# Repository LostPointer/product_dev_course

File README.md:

# Курс: Продуктовая разработка бэкенда

**ФАЛТ МФТИ | 2-3 курс**

## О курсе

Двухсеместровый практический курс по разработке современных бэкенд-систем с использованием Python, TypeScript и микросервисной архитектуры.

### Формат
- **Длительность:** 2 семестра (32 недели)
- **Нагрузка:** 1 пара (2 часа) в неделю
- **Формат:** Лекция + практика

### Технологический стек
- **Backend:** Python (aiohttp)
- **Frontend (для интеграции):** TypeScript, React
- **Базы данных:** PostgreSQL, Redis
- **Message Brokers:** RabbitMQ
- **Инфраструктура:** Docker, Docker Compose
- **CI/CD:** GitHub Actions
- **Тестирование:** pytest, testsuite (Yandex)
- **Мониторинг:** Prometheus, Grafana (базово)

## Структура курса

### Семестр 1: Основы бэкенд-разработки (14 учебных недель + 2 резерва)
1. **Модуль 1:** Веб-разработка и API (недели 1-4)
2. **Модуль 2:** Качество и тестирование (недели 5-7)
3. **Модуль 3:** Кэширование и производительность (недели 8-11)
4. **Модуль 4:** API контракты и интеграция с фронтендом (недели 12-14)
5. **Резервные недели:** 15-16 (каникулы, форс-мажоры, догоняющие занятия)

### Семестр 2: Микросервисы и продуктовая разработка (14 учебных недель + 2 резерва)
5. **Модуль 5:** Docker и деплой (недели 1-3)
6. **Модуль 6:** Микросервисная архитектура (недели 4-8)
7. **Модуль 7:** Продвинутые темы (недели 9-11)
8. **Модуль 8:** Финальный проект (недели 12-14)
9. **Резервные недели:** 15-16 (каникулы, форс-мажоры, защиты проектов)

## Навигация по репозиторию

```
product_dev_course/
├── course-materials/           # Материалы курса
│   ├── semester-1/
│   └── semester-2/
├── projects/
│   ├── backend/
│   │   ├── common/             # Общие компоненты и DTO
│   │   ├── libs/               # Внутренние библиотеки/SDK
│   │   └── services/           # Микросервисы платформы
│   │       ├── experiment-service/
│   │       └── auth-service/
│   ├── frontend/
│   │   ├── common/             # Общие UI-компоненты и токены
│   │   ├── libs/               # Фронтенд библиотеки
│   │   └── apps/               # SPA/виджеты
│   │       └── experiment-portal/
│   ├── telemetry_cli/          # CLI для отправки телеметрии в Experiment Service
│   └── rc_vehicle/             # Документация и материалы по RC-модели
├── docs/                       # Документация
├── examples/                   # Примеры кода с занятий
└── README.md
```

## Быстрый старт

### Предварительные требования
- Python 3.14+
- Node.js 24 LTS+
- Docker Desktop
- Git
- Любой редактор кода (VS Code рекомендуется)

### Установка окружения
```bash
# Клонирование репозитория
git clone <repository-url>
cd product_dev_course

# Настройка Python окружения
cd course-materials/semester-1/module-1-web-api/week-01
python -m venv venv
source venv/bin/activate  # Linux/Mac
# или
venv\Scripts\activate  # Windows

# Установка зависимостей
pip install -r requirements.txt
```

Подробная инструкция: [Setup Guide](docs/setup-guide.md)

## Локальный запуск через Docker

Для быстрого запуска всей системы локально используется Docker Compose.

### Быстрый старт с Docker

```bash
# 1. Подготовка окружения
cp env.docker.example .env
cp docker-compose.override.yml.example docker-compose.override.yml

# 2. Запуск в development режиме (с hot-reload)
docker-compose up

# 3. Или в фоновом режиме
docker-compose up -d

# 4. Просмотр логов
docker-compose logs -f

# 5. Остановка
docker-compose down
```

### Доступные сервисы

После запуска доступны:
- **Experiment Portal (Frontend):** http://localhost:3000 (dev режим с hot-reload)
- **Experiment Service API:** http://localhost:8002
- **Auth Service:** http://localhost:8001
- **Auth Proxy (BFF):** http://localhost:8080
- **Grafana (Logging):** http://localhost:3001 (логин: admin, пароль: admin)
- **PostgreSQL:** localhost:5433 (порт 5433 чтобы не конфликтовать с локальным PostgreSQL на 5432)
  - База данных `experiment_db` для experiment-service
  - База данных `auth_db` для auth-service

### Режимы работы

- **Development режим** (по умолчанию): hot-reload, volumes для исходного кода, dev команды
- **Production режим:** оптимизированные образы, без hot-reload
  ```bash
  docker-compose -f docker-compose.yml up
  ```

### Документация

Подробная документация по локальной разработке:
- [Инвентаризация сервисов](docs/local-dev-inventory.md)
- [Нормализация окружения](docs/local-dev-env-normalization.md)
- [Настройка Docker и hot-reload](docs/local-dev-docker-setup.md)
- [Ручное тестирование (E2E)](docs/manual-testing.md)

## Итоговый проект

Микросервисная система сбора и отображения экспериментов (Experiment Tracking Platform) с 6 сервисами на Python:
- Auth Service - аутентификация и управление пользователями, проектами
- Experiment Service - регистрация и хранение экспериментов
- Metrics Service - сбор и хранение метрик (accuracy, loss, и т.д.)
- Artifact Service - хранение артефактов (модели, графики, логи)
- Comparison Service - сравнение экспериментов
- API Gateway - единая точка входа, агрегация данных

Опционально: Frontend на TypeScript + React для визуализации экспериментов и дашбордов.

Студенты работают через Pull Requests, проводят code review и улучшают архитектуру системы.

**Техническое задание:** полное описание требований, архитектуры и критериев приемки доступно в `docs/experiment-tracking-ts.md`. Рекомендовано ознакомиться перед началом работы над итоговым проектом.

**Статус и roadmap платформы:** см. `docs/experiment-tracking-status-and-roadmap.md`.

## Карта сервисов

### Архитектурная диаграмма

```mermaid
graph TB
    subgraph Frontend["🌐 Frontend Layer"]
        Portal["Experiment Portal<br/>React SPA<br/>✅ Реализован<br/>:3000/:80"]
        AuthProxy["Auth Proxy<br/>nginx<br/>✅ Реализован<br/>:8080"]
    end

    subgraph GatewayLayer["🚪 API Gateway Layer"]
        Gateway["API Gateway<br/>Единая точка входа<br/>🚧 Планируется"]
    end

    subgraph Backend["⚙️ Backend Services"]
        AuthSvc["Auth Service<br/>Аутентификация, JWT<br/>🚧 Планируется"]
        ExpSvc["Experiment Service<br/>Эксперименты, запуски<br/>✅ Реализован<br/>:8002"]
        MetricsSvc["Metrics Service<br/>Метрики, временные ряды<br/>🚧 Планируется"]
        ArtifactSvc["Artifact Service<br/>Файлы, модели<br/>🚧 Планируется"]
        CompareSvc["Comparison Service<br/>Сравнение экспериментов<br/>🚧 Планируется"]
        TelemetrySvc["Telemetry Ingest<br/>Потоки телеметрии<br/>🚧 Планируется"]
    end

    subgraph Infrastructure["🏗️ Infrastructure"]
        Postgres[("PostgreSQL<br/>Основная БД<br/>:5432")]
        Redis[("Redis<br/>Кэш, rate limiting<br/>:6379")]
        RabbitMQ["RabbitMQ<br/>Message Broker<br/>:5672"]
        S3[("S3 Storage<br/>Артефакты<br/>🚧 Планируется")]
    end

    Portal -->|HTTP| AuthProxy
    AuthProxy -->|Proxy| Gateway
    Gateway -->|REST API| AuthSvc
    Gateway -->|REST API| ExpSvc
    Gateway -->|REST API| MetricsSvc
    Gateway -->|REST API| ArtifactSvc
    Gateway -->|REST API| CompareSvc

    TelemetrySvc -->|Publish| RabbitMQ
    RabbitMQ -->|Subscribe| MetricsSvc

    AuthSvc -->|SQL| Postgres
    ExpSvc -->|SQL| Postgres
    MetricsSvc -->|SQL| Postgres
    CompareSvc -->|SQL| Postgres
    TelemetrySvc -->|SQL| Postgres

    ArtifactSvc -->|Metadata| Postgres
    ArtifactSvc -->|Files| S3

    ExpSvc -->|Cache| Redis
    AuthSvc -->|Cache| Redis
    Gateway -->|Rate Limit| Redis

    ExpSvc -.->|Events| RabbitMQ
    MetricsSvc -.->|Events| RabbitMQ
    ArtifactSvc -.->|Events| RabbitMQ

    style ExpSvc fill:#90EE90,stroke:#2E7D32,stroke-width:3px
    style Portal fill:#90EE90,stroke:#2E7D32,stroke-width:3px
    style AuthProxy fill:#90EE90,stroke:#2E7D32,stroke-width:3px
    style AuthSvc fill:#FFE4B5,stroke:#FF8C00,stroke-width:2px
    style MetricsSvc fill:#FFE4B5,stroke:#FF8C00,stroke-width:2px
    style ArtifactSvc fill:#FFE4B5,stroke:#FF8C00,stroke-width:2px
    style CompareSvc fill:#FFE4B5,stroke:#FF8C00,stroke-width:2px
    style Gateway fill:#FFE4B5,stroke:#FF8C00,stroke-width:2px
    style TelemetrySvc fill:#FFE4B5,stroke:#FF8C00,stroke-width:2px
    style S3 fill:#FFE4B5,stroke:#FF8C00,stroke-width:2px
    style Postgres fill:#E3F2FD,stroke:#1976D2
    style Redis fill:#FFEBEE,stroke:#D32F2F
    style RabbitMQ fill:#F3E5F5,stroke:#7B1FA2
```

### Backend сервисы

| Сервис | Статус | Описание | Порт | База данных |
|--------|--------|----------|------|-------------|
| **Experiment Service** | ✅ Реализован | Регистрация и хранение экспериментов, запусков, capture sessions, датчиков | 8002 | PostgreSQL |
| **Auth Service** | 🚧 Планируется | Аутентификация и управление пользователями, проектами, JWT токены | - | PostgreSQL |
| **Metrics Service** | 🚧 Планируется | Сбор и хранение метрик (accuracy, loss и т.д.), исторические серии | - | PostgreSQL/Timescale |
| **Artifact Service** | 🚧 Планируется | Хранение артефактов (модели, графики, логи), версионирование | - | S3 + PostgreSQL |
| **Comparison Service** | 🚧 Планируется | Сравнение экспериментов, расчёт дельт по метрикам | - | PostgreSQL |
| **API Gateway** | 🚧 Планируется | Единая точка входа, агрегация данных от сервисов, маршрутизация | - | - |
| **Telemetry Ingest** | 🚧 Планируется | Приём потоков телеметрии, конвертация raw→physical значений | - | Kafka/Redis + PostgreSQL |

### Frontend приложения

| Приложение | Статус | Описание | Порт |
|------------|--------|----------|------|
| **Experiment Portal** | ✅ Реализован | React SPA для визуализации экспериментов и дашбордов | 3000 (dev), 80 (prod) |
| **Auth Proxy** | ✅ Реализован | Прокси для аутентификации и маршрутизации запросов | 8080 |

### Инфраструктурные сервисы

| Сервис | Описание | Порт |
|--------|----------|------|
| **PostgreSQL** | Основная база данных для всех сервисов | 5432 |
| **Redis** | Кэширование, rate limiting, сессии | 6379 |
| **RabbitMQ** | Message broker для event-driven коммуникации | 5672 (AMQP), 15672 (Management UI) |

### Легенда статусов
- ✅ **Реализован** - сервис полностью реализован и готов к использованию
- 🚧 **Планируется** - сервис в планах разработки

## Система оценивания

### Семестр 1 (50%)
- Практические задания: 30%
- Промежуточное тестирование: 10%
- Итоговое задание: 10%

### Семестр 2 (50%)
- Практические задания: 20%
- Pull Requests в проект: 20%
- Code Review: 5%
- Финальная защита: 5%

### Бонусы
- Рефакторинг кода: +5 баллов
- Добавление тестов: +5 баллов
- Улучшение документации: +5 баллов

### Шкала оценок (1-10)
- 10: Outstanding (95-115 баллов)
- 9: Excellent (90-94)
- 8: Very Good (85-89)
- 7: Good (75-84)
- 6: Satisfactory (65-74)
- 5: Adequate (55-64) - минимальный проходной
- 4 и ниже: не сдал

Подробнее: [Grading System](docs/grading-system.md)

## Полезные ресурсы

### Документация
- [aiohttp](https://docs.aiohttp.org/)
- [SQLAlchemy](https://docs.sqlalchemy.org/)
- [Docker](https://docs.docker.com/)
- [PostgreSQL](https://www.postgresql.org/docs/)
- [OpenAPI/Swagger](https://swagger.io/specification/)

### Книги
- "Designing Data-Intensive Applications" - Martin Kleppmann
- "Building Microservices" - Sam Newman
- "Clean Architecture" - Robert Martin

### Онлайн-курсы
- [aiohttp Tutorial](https://docs.aiohttp.org/en/stable/web_quickstart.html)
- [Docker for Beginners](https://docker-curriculum.com/)

## Связь

- **Вопросы по заданиям:** GitHub Issues в репозитории курса
- **Code Review:** Pull Requests в backend-project
- **Общие вопросы:** Telegram-чат курса

## Лицензия

Материалы курса доступны для образовательных целей.

---

**Добро пожаловать на курс! Удачи в изучении бэкенд-разработки! 🚀**

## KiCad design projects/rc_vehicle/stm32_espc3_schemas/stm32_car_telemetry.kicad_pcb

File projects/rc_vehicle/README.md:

# rc_vehicle

Проект про **управление RC‑моделью** (ретрофит): STM32 делает real‑time управление ESC/серво и сбор IMU, ESP32 поднимает Wi‑Fi (web‑пульт) и общается со STM32 по UART.

Сейчас здесь **документационный скелет**: требования, протоколы, договорённости. Реализация прошивок будет добавлена позже.

## Выбранная база (шасси)
- **Himoto SCT‑16 4WD RTR 1:16 2.4G (HI4192|RED)** — [карточка на Яндекс Маркете](https://market.yandex.ru/card/radioupravlyayemyy-short-kors-trak-himoto-sct-16-4wd-rtr-masshtab-116-24g---hi4192red/4399880474?do-waremd5=9jRAzA7SdRMQfoiYw52cAw&cpc=d2PGwzy0QTs0eLnRlKp0k5YCu2JHodVzFJDvJtshUWzSyDz3E9FKzWqRWc9gIULXX9EJ9Ku-0mvQsCTCCBzwqE-a6FjyS4PfsjEQ8zw1WU-FqmGO5HghkO4aplP4qdbhCmxXetVCLQqycN6o03nHXP_tLSTfOP2glbQ73t_oCvPUAJbjP6PtzyvAx9EZdLsM_MZD6JCx9hF2cmhA0Yc88aMXOZ_Ei1IVvZjbvcsvgHDewTubfOP7WxmSPsCnzZvbiXsTE30oPZ2PX6ct5WAkjK3DLf9791pMdJqhKAAkwv7LcDElOfELc6S0wxkUen63wrtSxWiKAo38hVIlcprRM84HQu9ao5TKsC9LjxYBM0hP5J5NaEfI0IHukClWKjyg9bwUETyJZKEokhHrUvGdfPVfDCgSMMCBr0cFhxl4T4GRgdt4k6KP_xjqOGhNoV-7&ogV=-9)

## Telemetry agent
CLI/агент для отправки телеметрии в Experiment Service вынесен в отдельный проект:
- `projects/telemetry_cli`

## Область ответственности
- управление (RC‑пульт и Wi‑Fi), приоритет RC > Wi‑Fi
- failsafe при потере источника управления
- IMU чтение и выдача телеметрии в web‑пульт (и/или наружу в будущем)

## Документация
- `docs/ts.md` — краткое ТЗ и критерии приёмки (MVP).
- `docs/interfaces_protocols.md` — протоколы: WebSocket (ESP32↔браузер) и UART кадры (ESP32↔RP2040).
- `docs/wiring_diagram.md` — **схема подключения компонентов** (ESP32, RP2040, IMU, ESC, Servo, RC приёмник).
- `docs/wiring_diagram.drawio` — визуальная схема для редактирования в draw.io.
- `docs/ai_schematic_tools.md` — инструменты и AI для генерации схем.
- `docs/glossary_ru.md` — глоссарий терминов и сокращений (ESC, BEC, PWM, IMU и т.д.).
- `docs/cpp_coding_style.md` — стиль кода для прошивок (C++): Google Style Guide, расширения `.hpp`, правила форматирования.
- `docs/firmware_timing.md` — тайминги и частоты для прошивок.
- `docs/stabilization/` — документация системы стабилизации (роудмап разработки).
- (вне проекта) `docs/telemetry-rc-stm32.md` — рекомендации по формату телеметрии для Experiment Service, если будем экспортировать данные в ingest.

## Структура проекта
- `firmware/rp2040/` — прошивка RP2040 (PWM, RC‑in, IMU, failsafe, UART протокол) — *в разработке*
- `firmware/esp32/` — прошивка ESP32‑S3 (AP + web UI + WS + UART мост) — *в разработке*
- `docs/` — спецификации и схемы
  - `firmware_timing.md` — тайминги и частоты для прошивок

## Сборка прошивок

Для удобной сборки обеих прошивок используется Makefile в корне проекта:

```bash
# Показать все доступные команды
make help

# Собрать обе прошивки
make all

# Собрать только ESP32
make esp32-build

# Собрать только RP2040
make rp2040-build

# Очистить все проекты
make clean
```

Подробные инструкции по сборке каждой прошивки:
- ESP32: см. `firmware/esp32/README.md`
- RP2040: см. `firmware/rp2040/README.md`

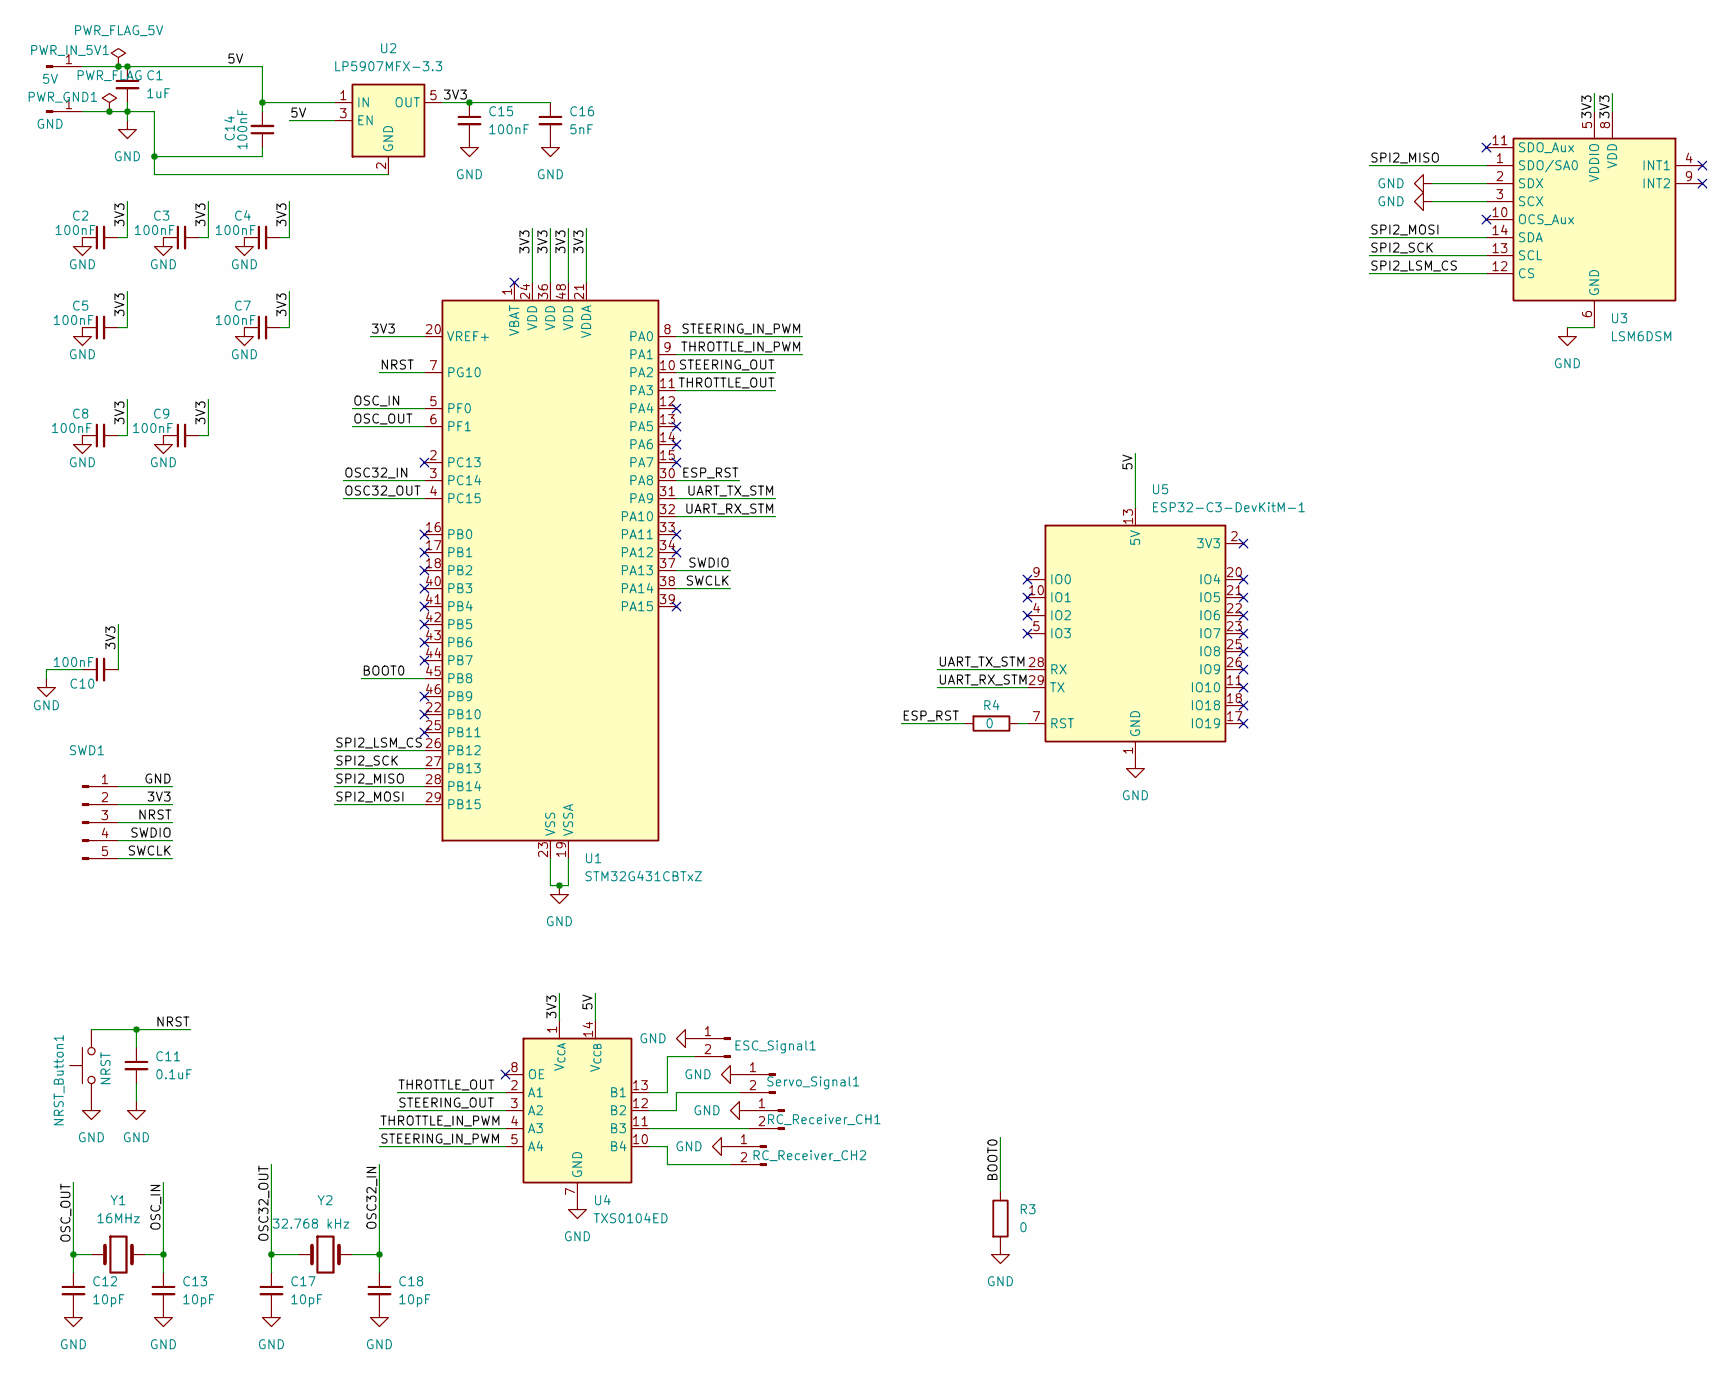
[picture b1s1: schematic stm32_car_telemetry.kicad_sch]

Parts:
C1: 1uF; C_0805_2012Metric
C2, C3, C4, C5, C7, C8, C9, C10: 100nF; C_0201_0603Metric
C11: 0.1uF; C_0805_2012Metric
C12, C13, C17, C18: 10pF; C_01005_0402Metric
C14, C15: 100nF; C_0805_2012Metric
C16: 5nF; C_0805_2012Metric
ESC_Signal1: Conn_01x02_Pin; PinHeader_1x02_P2.54mm_Vertical
NRST_Button1: NRST; SW_SPST_PTS810
PWR_GND1: GND; PinSocket_1x01_P2.54mm_Vertical
PWR_IN_5V1: 5V; PinSocket_1x01_P2.54mm_Vertical
R3, R4: 0; R_0201_0603Metric
RC_Receiver_CH1, RC_Receiver_CH2: Conn_01x02_Pin; PinHeader_1x02_P2.54mm_Vertical
SWD1: Conn_01x05_Pin; PinHeader_1x05_P2.54mm_Vertical
Servo_Signal1: Conn_01x02_Pin; PinHeader_1x02_P2.54mm_Vertical
U1: STM32G431CBTxZ; LQFP-48_7x7mm_P0.5mm
U2: LP5907MFX-3.3; SOT-23-5
U3: LSM6DSM; LGA-14_3x2.5mm_P0.5mm_LayoutBorder3x4y
U4: TXS0104ED; SOIC-14_3.9x8.7mm_P1.27mm
U5: ESP32-C3-DevKitM-1
Y1: 16MHz; Crystal_SMD_3225-4Pin_3.2x2.5mm
Y2: 32.768 kHz; Crystal_SMD_3225-4Pin_3.2x2.5mm

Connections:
/3V3: C2.2, C3.2, C4.2, C5.2, C7.2, C8.2, C9.2, C10.2, C15.1, C16.1, SWD1.2, U1.20 (VREF+), U1.21 (VDDA), U1.24 (VDD), U1.36 (VDD), U1.48 (VDD), U2.5 (OUT), U3.5 (VDDIO), U3.8 (VDD), U4.1 (V_{CCA})
/5V: C1.1, C14.2, PWR_IN_5V1.1, U2.1 (IN), U2.3 (EN), U4.14 (V_{CCB}), U5.13 (5V), U5.14 (5V)
/BOOT0: R3.1, U1.45 (PB8)
/ESP_RST: R4.2, U1.30 (PA8)
/NRST: C11.1, NRST_Button1.2, SWD1.3, U1.7 (PG10)
/OSC32_IN: C18.1, U1.3 (PC14), Y2.2
/OSC32_OUT: C17.1, U1.4 (PC15), Y2.1
/OSC_IN: C13.1, U1.5 (PF0), Y1.2
/OSC_OUT: C12.1, U1.6 (PF1), Y1.1
/SPI2_LSM_CS: U1.26 (PB12), U3.12 (CS)
/SPI2_MISO: U1.28 (PB14), U3.1 (SDO/SA0)
/SPI2_MOSI: U1.29 (PB15), U3.14 (SDA)
/SPI2_SCK: U1.27 (PB13), U3.13 (SCL)
/STEERING_IN_PWM: U1.8 (PA0), U4.5 (A4)
/STEERING_OUT: U1.10 (PA2), U4.3 (A2)
/SWCLK: SWD1.5, U1.38 (PA14)
/SWDIO: SWD1.4, U1.37 (PA13)
/THROTTLE_IN_PWM: U1.9 (PA1), U4.4 (A3)
/THROTTLE_OUT: U1.11 (PA3), U4.2 (A1)
/UART_RX_STM: U1.32 (PA10), U5.29 (TX)
/UART_TX_STM: U1.31 (PA9), U5.28 (RX)
GND: C1.2, C2.1, C3.1, C4.1, C5.1, C7.1, C8.1, C9.1, C10.1, C11.2, C12.2, C13.2, C14.1, C15.2, C16.2, C17.2, C18.2, ESC_Signal1.1, NRST_Button1.1, PWR_GND1.1, R3.2, RC_Receiver_CH1.1, RC_Receiver_CH2.1, SWD1.1, Servo_Signal1.1, U1.19 (VSSA), U1.23 (VSS), U1.35 (VSS), U1.47 (VSS), U2.2 (GND), U3.2 (SDX), U3.3 (SCX), U3.6 (GND), U3.7 (GND), U4.7 (GND), U5.1 (GND), U5.6 (GND), U5.8 (GND), U5.12 (GND), U5.15 (GND), U5.16 (GND), U5.19 (GND), U5.24 (GND), U5.27 (GND), U5.30 (GND)
unnamed: ESC_Signal1.2, U4.13 (B1)
unnamed: RC_Receiver_CH1.2, U4.11 (B3)
unnamed: RC_Receiver_CH2.2, U4.10 (B4)
unnamed: Servo_Signal1.2, U4.12 (B2)
unnamed: R4.1, U5.7 (RST)

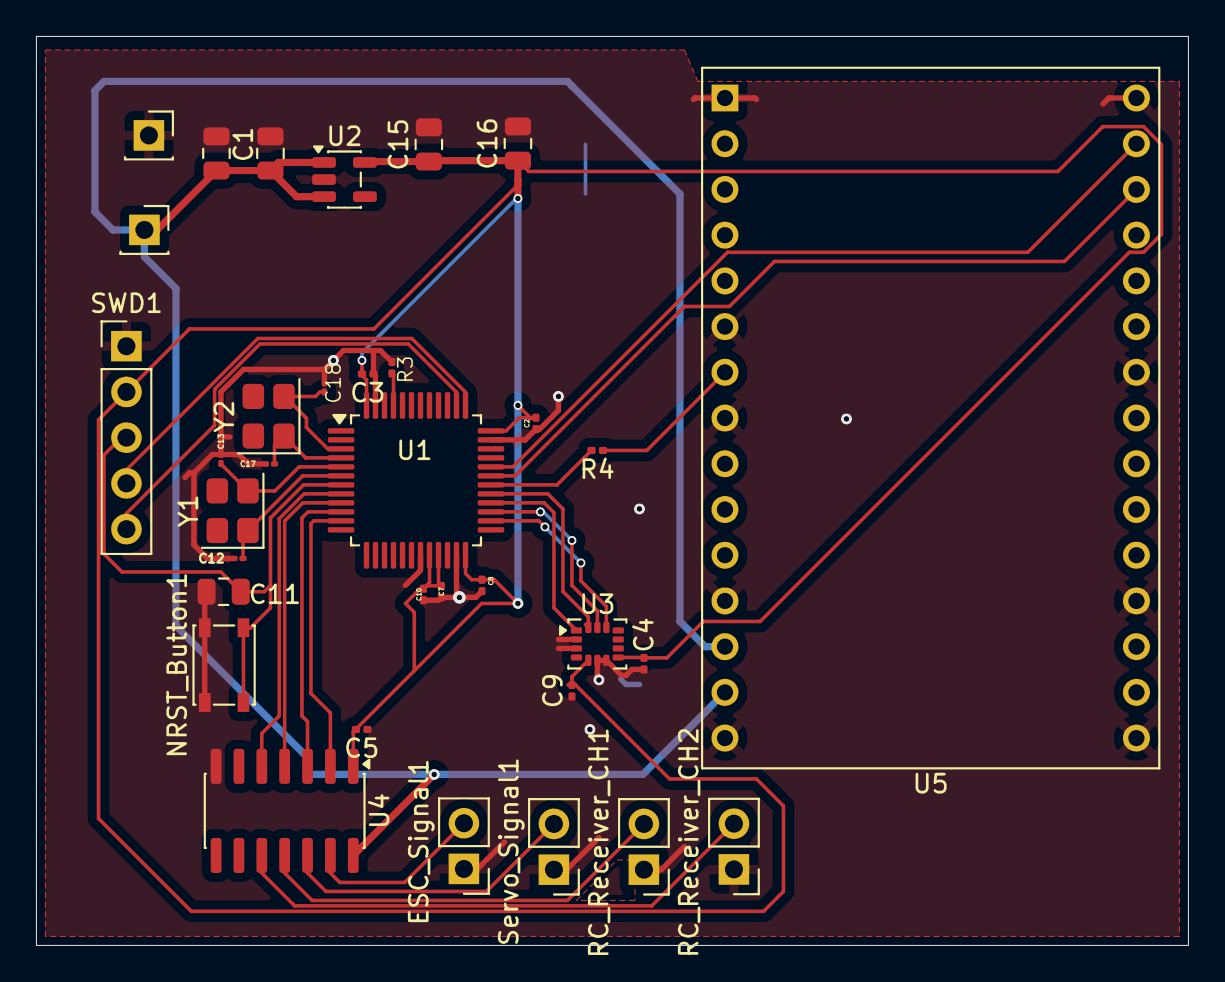
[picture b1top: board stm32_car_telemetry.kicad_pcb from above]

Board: 2 copper layers, 64.0 x 50.5 mm, 34 parts (0 on the bottom side), 27 nets.

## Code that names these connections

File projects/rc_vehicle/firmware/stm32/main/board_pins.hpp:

#pragma once

// Пины и периферия по семейству MCU (STM32Cube LL).
// Используются в uart_bridge, pwm_control, rc_input, imu (SPI).
// Порты: GPIOA, GPIOB (STM32Cube). Пины: номер 0..15 или маска LL_GPIO_PIN_x.

#if !defined(STM32F1) && !defined(STM32F4) && !defined(STM32G4)
#define STM32F1 1  // Fallback для IDE
#endif

#if defined(STM32F1)
// Blue Pill STM32F103C8: USART2 (PA2/PA3), TIM2 CH1/CH2 (PA0/PA1), RC-in PA4/PA5, IMU SPI2 PB12/PB13/PB14/PB15
#define UART_USART       USART2
#define UART_GPIO_PORT   GPIOA
#define UART_TX_PIN      2
#define UART_RX_PIN      3
#define PWM_TIM          TIM2
#define PWM_THROTTLE_PORT GPIOA
#define PWM_THROTTLE_PIN  0
#define PWM_STEERING_PORT GPIOA
#define PWM_STEERING_PIN  1
#define RC_IN_THROTTLE_PORT  GPIOA
#define RC_IN_THROTTLE_PIN   4
#define RC_IN_STEERING_PORT  GPIOA
#define RC_IN_STEERING_PIN   5
// IMU MPU-6050 по SPI2 (PB13 SCK, PB14 MISO, PB15 MOSI, PB12 NCS)
#define SPI_PERIPH       SPI2
#define SPI_SCK_PORT     GPIOB
#define SPI_SCK_PIN      13
#define SPI_MISO_PORT    GPIOB
#define SPI_MISO_PIN     14
#define SPI_MOSI_PORT    GPIOB
#define SPI_MOSI_PIN     15
#define SPI_NCS_PORT     GPIOB
#define SPI_NCS_PIN      12

#elif defined(STM32F4)
// Black Pill STM32F411: USART2 (PA2/PA3), TIM2 CH1/CH2 (PA0/PA1), RC-in PA4/PA5, IMU SPI2 PB12–PB15
#define UART_USART       USART2
#define UART_GPIO_PORT   GPIOA
#define UART_TX_PIN      2
#define UART_RX_PIN      3
#define PWM_TIM          TIM2
#define PWM_THROTTLE_PORT GPIOA
#define PWM_THROTTLE_PIN  0
#define PWM_STEERING_PORT GPIOA
#define PWM_STEERING_PIN  1
#define RC_IN_THROTTLE_PORT  GPIOA
#define RC_IN_THROTTLE_PIN   4
#define RC_IN_STEERING_PORT  GPIOA
#define RC_IN_STEERING_PIN   5
// IMU MPU-6050 по SPI2
#define SPI_PERIPH       SPI2
#define SPI_SCK_PORT     GPIOB
#define SPI_SCK_PIN      13
#define SPI_MISO_PORT    GPIOB
#define SPI_MISO_PIN     14
#define SPI_MOSI_PORT    GPIOB
#define SPI_MOSI_PIN     15
#define SPI_NCS_PORT     GPIOB
#define SPI_NCS_PIN      12

#elif defined(STM32G4)
// STM32G431CB: USART2 (PA2/PA3), TIM2, RC-in, IMU SPI2 — настройте под схему
#define UART_USART       USART2
#define UART_GPIO_PORT   GPIOA
#define UART_TX_PIN      2
#define UART_RX_PIN      3
#define PWM_TIM          TIM2
#define PWM_THROTTLE_PORT GPIOA
#define PWM_THROTTLE_PIN  0
#define PWM_STEERING_PORT GPIOA
#define PWM_STEERING_PIN  1
#define RC_IN_THROTTLE_PORT  GPIOA
#define RC_IN_THROTTLE_PIN   4
#define RC_IN_STEERING_PORT  GPIOA
#define RC_IN_STEERING_PIN   5
// IMU MPU-6050 по SPI2
#define SPI_PERIPH       SPI2
#define SPI_SCK_PORT     GPIOB
#define SPI_SCK_PIN      13
#define SPI_MISO_PORT    GPIOB
#define SPI_MISO_PIN     14
#define SPI_MOSI_PORT    GPIOB
#define SPI_MOSI_PIN     15
#define SPI_NCS_PORT     GPIOB
#define SPI_NCS_PIN      12

#else
#error "Не задано семейство MCU (STM32F1, STM32F4, STM32G4). Проверьте cmake/boards/"
#endif

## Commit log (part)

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2025-12-03 feat: enforce status transitions and idempotency
2025-12-03 Add sensor services and OpenAPI docs
2025-12-06 Implement run metrics ingest/query endpoints
2025-12-12 docs: добавлена карта сервисов с архитектурной диаграммой (#19)
2025-12-12 fix: add type ignore for untyped import in main.py
    - Added a type ignore comment for the aiohttp_cors import to resolve type checking issues.
2025-12-12 fix: исправлены CORS и пути API для фронтенда
    - Исправлен порядок инициализации CORS в experiment-service (настройка CORS до добавления роутов)
    - Обновлены пути API в фронтенд-клиенте с /experiments на /api/v1/experiments
    - Обновлены пути для runs API с /runs на /api/v1/runs
    - Исправлен HTTP метод для update с PUT на PATCH (соответствует бэкенду)
    - Исправлены методы complete и fail для использования PATCH с правильными данными
    Fixes: CORS ошибки и 404 ошиб
2025-12-25 refactor: move backend and frontend under projects
2025-12-26 docs: add docs index and telemetry-cli TS
2025-12-26 feat: implement experiment search endpoint
    - Add search_experiments method to ExperimentRepository with ILIKE search on name and description
    - Add search_experiments method to ExperimentService
    - Add GET /api/v1/experiments/search endpoint with query parameter 'q'
    - Update OpenAPI specification with search endpoint definition
    - Update BACKEND_MVP_STATUS.md to reflect search implementation
    Fixes missing search functionality required by frontend
2025-12-26 feat: добавлена поддержка trace_id и request_id для логирования и трассировки
    - Добавлена генерация trace_id и request_id на frontend (experiment-portal)
    - Добавлены interceptors в API клиентах для автоматической передачи заголовков
    - Реализован middleware для извлечения и логирования trace_id/request_id в auth-proxy
    - Реализован middleware для извлечения и логирования trace_id/request_id в auth-service и experiment-service
    - Настроено структурированное JSON логирован
2025-12-26 fix: исправление всех падающих тестов
    - Обновлены тесты CreateExperiment для работы с модальным окном CreateExperimentModal
    - Исправлен тест App.test.tsx для удаленного маршрута /experiments/new
    - Добавлен мок interceptors.request в тестах API (auth, client, sensors)
    - Все тесты теперь проходят (178 passed)
2025-12-26 Добавлена правильная типизация для mypy вместо игнорирования
    - Добавлен файл py.typed в backend_common для указания поддержки типизации
    - Добавлен stub файл для asyncpg в types/asyncpg/__init__.pyi
    - Настроен mypy_path для использования локальных stub файлов
    - Убрано глобальное ignore_missing_imports, теперь типы проверяются правильно
    - type-check теперь проходит успешно без игнорирования ошибок
2025-12-26 feat: add auth-service tests to CI workflow
    - Add auth-service test job to GitHub Actions
    - Remove generate-sdk job (temporarily disabled)
    - Both auth-service and experiment-service tests now run in parallel
2025-12-29 docs: add new documentation files
    - Add ESP32-S3 setup guide
    - Add backend TODO list
    - Add coding style guidelines for RC vehicle project
    - Add C++ coding style guidelines
    - Add firmware timing documentation
2026-01-12 chore(auth-proxy): debug log X-Project-* headers
2026-01-13 feat(frontend): improve experiment creation flow
2026-01-13 test(experiment-service): fix RunService ctor in storage layer test
2026-01-13 chore(experiment-service): remove telemetry ingest endpoints
2026-01-13 feat(frontend): live telemetry SSE stream modal
2026-01-13 feat(frontend): send CSRF token header automatically
2026-01-13 docs: add manual E2E testing guide
    - add docs/manual-testing.md (portal→auth-proxy→services→db)
    - link from README and docs index
    - add experiment-service migration for webhook tables
2026-01-29 firmware(stm32): add STM32 platform
    - Add CMake build with board support (F103, F401, F411, G431)
    - Add main: uart_bridge (common base), failsafe, IMU, PWM, RC input
    - Add platform abstraction, config, README
2026-01-29 docs: unify status/roadmap into single source of truth
    Add consolidated Experiment Tracking status+roadmap doc, update references, and keep old MVP/roadmap files as redirects.
2026-01-29 docker-compose: wire auth-service and telemetry URLs via env
2026-01-29 frontend: add capture session telemetry history
2026-01-29 chore: update services and docker setup
2026-01-29 style(experiment-portal): introduce theme tokens and refresh styles
2026-01-29 docs: mark loading states as done in experiment-tracking roadmap
2026-01-29 docs: add android client backlog item
    Track the Android client idea in the experiment tracking roadmap.
2026-01-29 frontend: stabilize MaterialSelect tests
    Add a helper for MaterialSelect interactions and update affected component and
    page tests to use the button/listbox flow.
2026-02-06 firmware(stm32): IMU по SPI, SpiStm32, общий failsafe и утилиты
    - board_pins: SPI2 (PB12 NCS, PB13/14/15), убран I2C для IMU
    - config: убран I2C, IMU по SPI
    - cube_ll_sources: ll_spi вместо ll_i2c
    - spi_stm32: реализация SpiBase (STM32Cube LL)
    - imu: Mpu6050Spi + SpiStm32, общий C-API
    - failsafe: обёртка над rc_vehicle::failsafe_core
2026-02-11 refactor: disable password complexity validation in test environment
    Add PASSWORD_COMPLEXITY_ENABLED flag to auth_service.domain.dto that
    is set to False in test conftest.py. This allows tests to use simple
    passwords (like 'testpass123') while production still enforces
    complexity (uppercase + lowercase + digit).
    Revert test passwords back to their original simple values.
2026-03-01 fix(experiment-service): return 404 for missing run/session in telemetry export
    - Catch NotFoundError in export_session_telemetry and export_run_telemetry
    - Add integration tests for telemetry export API (CSV/JSON, filters, RBAC)
    Made-with: Cursor
2026-03-02 firmware(rc_vehicle): add tests for adaptive PID, oversteer, TelemetryLog
    Made-with: Cursor
2026-03-02 chore(claude): add frontend type-check and test to local settings
    Made-with: Cursor
2026-03-03 firmware: удаление мёртвого кода и унификация конфигурации
    - Удалены неиспользуемые файлы: base_component.hpp, config_common.hpp,
    context.hpp, vehicle_control.hpp
    - common/config.hpp: единый источник констант (SlewRate, DiagnosticsConfig),
    vehicle_control_unified.cpp подключает config.hpp вместо локальных копий
    - esp32_s3/main: убран include config_common.hpp
    - README common: убраны ссылки на удалённые context/base_component
2026-03-03 firmware: Phase 1 refactoring - config constants, DelayUntilNextTick fix, namespace additions
    - Added TelemetryLogConfig and LpfConfig to config.hpp with named constants
    - Fixed static variable in DelayUntilNextTick() - moved to instance members for thread safety
    - Added rc_vehicle namespace to MadgwickFilter and ImuCalibration classes
    - Updated REFACTORING_PROPOSAL.md to track completed items
    - Removed old REFACTORING.md, replaced with detailed REFACTORING_PROPOSAL.md
    Phase 1: Quick Wins (3/3 completed)
2026-03-06 fix(tests): исправить тесты experiment-service
    - state_machine.py: добавить ARCHIVED: set() для terminal states (78 тестов ✅)
    - test_webhooks_dispatcher.py:
    - import asyncio
    - session = MagicMock() вместо AsyncMock()
    - response.text = AsyncMock()
    - fix test_attempt_6 assertion
2026-03-07 feat(branding): переименовать Lab Atlas в Bartini Labs
    - Обновить название в sidebar бренда
    - Lab Atlas → Bartini Labs
2026-03-10 chore(test): печатать общий итог pytest в make test-backend
    Добавляет агрегацию passed/failed по всем backend-сервисам и выводит итоговую строку в конце прогона, сохраняя корректный exit code.
    Made-with: Cursor
2026-03-11 chore: docker-compose, experiment-service routes, auth/telemetry tests
    - docker-compose and override example updates
    - experiment-service: capture_sessions, runs, dependencies
    - auth-service: integration conftest, root conftest
    - telemetry-ingest-service: test_health
    - infrastructure/logging docker-compose
    - .claude/settings.local.json
2026-03-14 rc_vehicle: fix self_test, update esp32_s3 CMakeLists
    Made-with: Cursor
2026-03-15 feat: добавить детальное логирование при ошибке валидации конфигурации
    - ESP_LOGE с подробностями: magic, валидность подконфигов, параметры PID
    - Помогает отладить проблемы с Invalid stabilization config
2026-03-17 docs: добавить README для backend-common и обновить документацию
    - Добавить README.md для backend-common
    - Обновить docs/experiment-tracking-ts.md
2026-03-21 chore(claude): add new allowed shell commands for script execution and testing
2026-03-21 docs(scripts): add script-execution architecture and update implementation plan
2026-03-29 fix(firmware): restore ESP32 link and telemetry log HTTP API
    - Add VehicleControlGetLogInfo / VehicleControlGetLogFrame wrappers in
    vehicle_control.hpp for GET /api/log.bin in http_server.
    - Register missing common sources in main/CMakeLists.txt (init, auto drive,
    calibrations, control loop, telemetry builder) so the IDF build links.
    Made-with: Cursor
2026-04-10 fix: firmware fix download telemetry file
2026-04-17 feat: add rfc for config-service
2026-04-20 docs(rfc): RFC-0001 config-service review (#56)
2026-04-23 docs(tasks): restore and expand ideas backlog (#60)
2026-05-05 refactor(mutations): migrate 3 modals to useApiMutation (ETAP 5b/5c) (#74)
2026-05-06 refactor: ETAP 9b/9c — decompose Scripts.tsx and ProjectMembersModal.tsx (#78)
2026-05-06 feat(auth-proxy): ETAP 10b — proxyFactory for repetitive httpProxy registrations (#81)
2026-05-07 test(script-service): unit tests for dependencies module (29 tests) (#85)
2026-05-08 test(script-service): extend executions routes with validation/RBAC tests (+16) (#87)
2026-05-08 test(firmware): GTest for drive_mode_registry and auto_drive_coordinator (#91)
2026-05-08 test(experiment-portal): unit tests for Register/ResetPassword/ChangePassword (+20) (#96)
2026-05-08 test: close remaining Phase 5 gaps — 3 page tests + coverage gates (#102)
2026-05-09 fix(telemetry-ingest): don't leak exception strings in HTTP/SSE responses (#107)
2026-05-09 fix(experiment-service): don't leak exception strings in HTTP responses (-79 alerts) (#109)
2026-05-09 ci(auth/telemetry): shard pytest across 2 parallel runners (#113)
